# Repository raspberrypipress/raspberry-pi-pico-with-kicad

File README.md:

# Design an RP2040 board with KiCad

Example code and assets for Design an RP2040 board with KiCad from Raspberry Pi Press

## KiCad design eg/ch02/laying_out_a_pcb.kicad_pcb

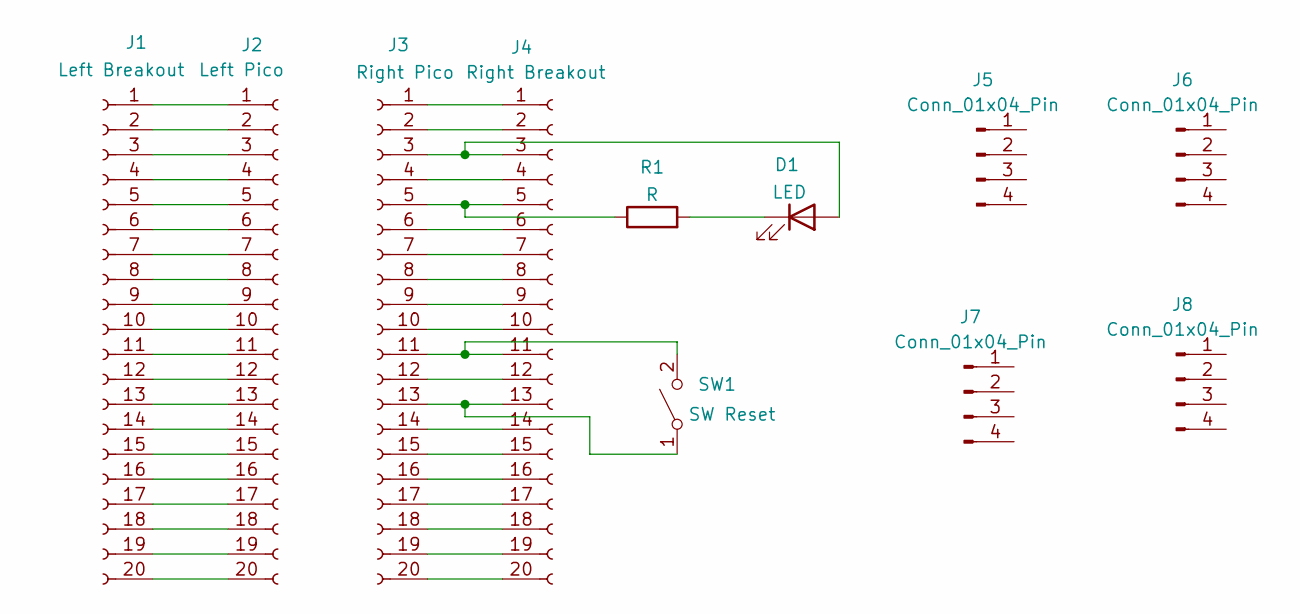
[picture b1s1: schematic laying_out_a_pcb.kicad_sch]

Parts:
D1: LED; LED_0805_2012Metric
J1: Left Breakout; PinSocket_1x20_P2.54mm_Vertical
J2: Left Pico; PinSocket_1x20_P2.54mm_Vertical
J3: Right Pico; PinSocket_1x20_P2.54mm_Vertical
J4: Right Breakout; PinSocket_1x20_P2.54mm_Vertical
J5, J6, J7, J8: Conn_01x04_Pin; PinSocket_1x04_P2.54mm_Vertical
R1: R; R_0805_2012Metric
SW1: SW Reset; SW_SPST_B3SL-1002P

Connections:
unnamed 0: D1.2 (A), J3.3, J4.3; also elsewhere on the board
unnamed 1: D1.1 (K), R1.2; also elsewhere on the board
unnamed: J1.1, J2.1
unnamed: J1.2, J2.2
unnamed: J1.3, J2.3
unnamed: J1.4, J2.4
unnamed: J1.5, J2.5
unnamed: J1.6, J2.6
unnamed: J1.7, J2.7
unnamed: J1.8, J2.8
unnamed: J1.9, J2.9
unnamed: J1.10, J2.10
unnamed: J1.11, J2.11
unnamed: J1.12, J2.12
unnamed: J1.13, J2.13
unnamed: J1.14, J2.14
unnamed: J1.15, J2.15
unnamed: J1.16, J2.16
unnamed: J1.17, J2.17
unnamed: J1.18, J2.18
unnamed: J1.19, J2.19
unnamed: J1.20, J2.20
unnamed: J3.1, J4.1
unnamed: J3.2, J4.2
unnamed: J3.4, J4.4
unnamed: J3.5, J4.5, R1.1
unnamed: J3.6, J4.6
unnamed: J3.7, J4.7
unnamed: J3.8, J4.8
unnamed: J3.9, J4.9
unnamed: J3.10, J4.10
unnamed: J3.11, J4.11, SW1.2 (B)
unnamed: J3.12, J4.12
unnamed: J3.13, J4.13, SW1.1 (A)
unnamed: J3.14, J4.14
unnamed: J3.15, J4.15
unnamed: J3.16, J4.16
unnamed: J3.17, J4.17
unnamed: J3.18, J4.18
unnamed: J3.19, J4.19
unnamed: J3.20, J4.20

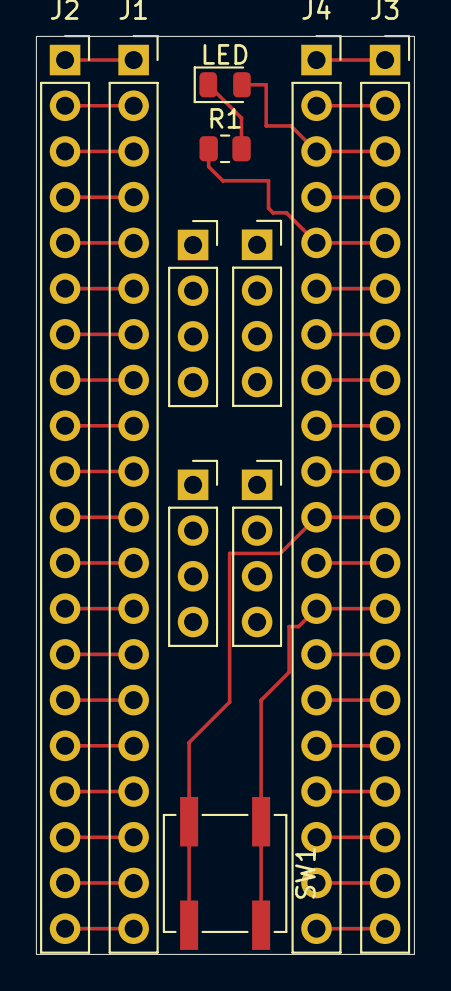
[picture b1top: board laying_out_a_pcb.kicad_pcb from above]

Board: 2 copper layers, 21.0 x 51.0 mm, 11 parts (0 on the bottom side), 41 nets.

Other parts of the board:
LED: LED; LED_0805_2012Metric

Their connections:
unnamed 0: LED.2 (A); also elsewhere on the board
unnamed 1: LED.1 (K); also elsewhere on the board

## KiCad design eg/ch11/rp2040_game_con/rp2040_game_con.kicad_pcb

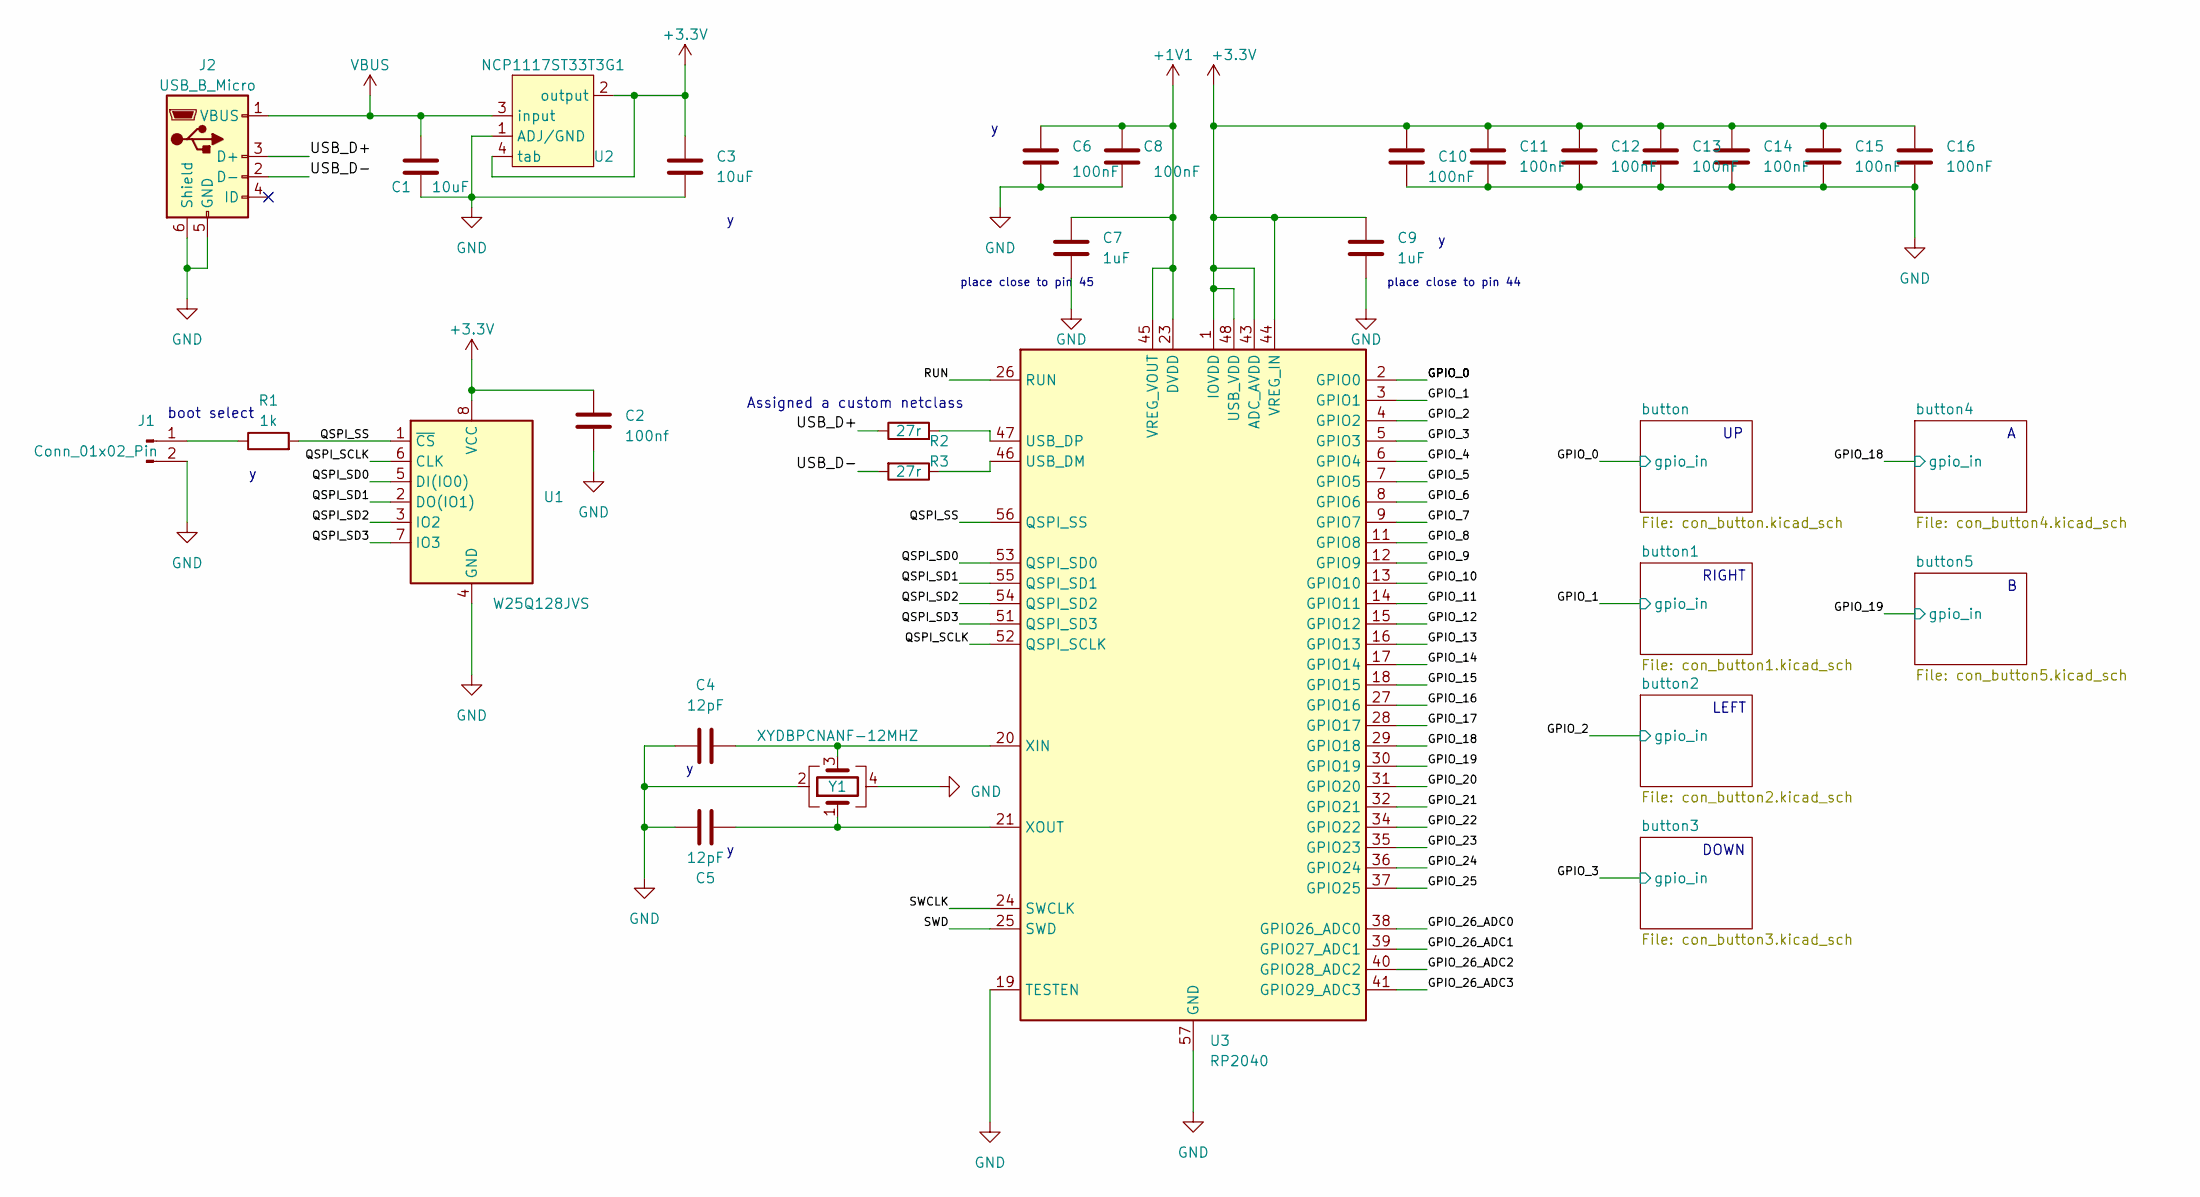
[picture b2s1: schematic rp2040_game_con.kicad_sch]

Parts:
C1, C3: 10uF; C_1206_3216Metric; LCSC C13585
C2: 100nf; C_0402_1005Metric; LCSC C1525
C4, C5: 12pF; C_0402_1005Metric; LCSC C1547
C6, C8, C10, C11, C12, C13, C15, C16: 100nF; C_0402_1005Metric; LCSC C1525
C7, C9: 1uF; C_0402_1005Metric; LCSC C52923
C14: 100nF; C_0402_1005Metric; JLCPCBA Part # C1525
J1: Conn_01x02_Pin; PinHeader_1x02_P2.54mm_Vertical
J2: USB_B_Micro; MICRO-USB-SMD_C393940; LCSC C393940
R1: 1k; R_0402_1005Metric; LCSC C279981
R2, R3: 27r; R_0402_1005Metric; LCSC C2909343
U1: W25Q128JVS; SOIC-8_5.23x5.23mm_P1.27mm; LCSC C97521
U2: NCP1117ST33T3G1; SOT-223; LCSC C6186
U3: RP2040; QFN-56-1EP_7x7mm_P0.4mm_EP3.2x3.2mm; LCSC C2040
Y1: XYDBPCNANF-12MHZ; Xstal_2520_4P_XYDBPCNANF-12MHZ; LCSC C521567

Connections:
+1V1: C6.1, C7.1, C8.1, U3.23 (DVDD), U3.45 (VREG_VOUT), U3.50 (DVDD)
+3.3V: C2.1, C3.1, C9.1, C10.1, C11.1, C12.1, C13.1, C14.1, C15.1, C16.1, U1.8 (VCC), U2.2 (output), U2.4 (tab), U3.1 (IOVDD), U3.10 (IOVDD), U3.22 (IOVDD), U3.33 (IOVDD), U3.42 (IOVDD), U3.43 (ADC_AVDD), U3.44 (VREG_IN), U3.48 (USB_VDD), U3.49 (IOVDD)
/GPIO_0: U3.2 (GPIO0); also elsewhere on the board
/GPIO_1: U3.3 (GPIO1); also elsewhere on the board
/GPIO_2: U3.4 (GPIO2); also elsewhere on the board
/GPIO_3: U3.5 (GPIO3); also elsewhere on the board
/GPIO_4: U3.6 (GPIO4)
/GPIO_5: U3.7 (GPIO5)
/GPIO_6: U3.8 (GPIO6)
/GPIO_7: U3.9 (GPIO7)
/GPIO_8: U3.11 (GPIO8)
/GPIO_9: U3.12 (GPIO9)
/GPIO_10: U3.13 (GPIO10)
/GPIO_11: U3.14 (GPIO11)
/GPIO_12: U3.15 (GPIO12)
/GPIO_13: U3.16 (GPIO13)
/GPIO_14: U3.17 (GPIO14)
/GPIO_15: U3.18 (GPIO15)
/GPIO_16: U3.27 (GPIO16)
/GPIO_17: U3.28 (GPIO17)
/GPIO_18: U3.29 (GPIO18); also elsewhere on the board
/GPIO_19: U3.30 (GPIO19); also elsewhere on the board
/GPIO_20: U3.31 (GPIO20)
/GPIO_21: U3.32 (GPIO21)
/GPIO_22: U3.34 (GPIO22)
/GPIO_23: U3.35 (GPIO23)
/GPIO_24: U3.36 (GPIO24)
/GPIO_25: U3.37 (GPIO25)
/GPIO_26_ADC0: U3.38 (GPIO26_ADC0)
/GPIO_26_ADC1: U3.39 (GPIO27_ADC1)
/GPIO_26_ADC2: U3.40 (GPIO28_ADC2)
/GPIO_26_ADC3: U3.41 (GPIO29_ADC3)
/QSPI_SCLK: U1.6 (CLK), U3.52 (QSPI_SCLK)
/QSPI_SD0: U1.5 (DI(IO0)), U3.53 (QSPI_SD0)
/QSPI_SD1: U1.2 (DO(IO1)), U3.55 (QSPI_SD1)
/QSPI_SD2: U1.3 (IO2), U3.54 (QSPI_SD2)
/QSPI_SD3: U1.7 (IO3), U3.51 (QSPI_SD3)
/QSPI_SS: R1.2, U1.1 (~CS), U3.56 (QSPI_SS)
/RUN: U3.26 (RUN)
/SWCLK: U3.24 (SWCLK)
/SWD: U3.25 (SWD)
/USB_D+: J2.3 (D+), R2.1
/USB_D-: J2.2 (D-), R3.2
GND: C1.2, C2.2, C3.2, C4.1, C5.1, C6.2, C7.2, C8.2, C9.2, C10.2, C11.2, C12.2, C13.2, C14.2, C15.2, C16.2, J1.2, J2.5 (GND), J2.6 (Shield), U1.4 (GND), U2.1 (ADJ/GND), U3.19 (TESTEN), U3.57 (GND), Y1.2, Y1.4; also elsewhere on the board
unnamed: J1.1, R1.1
unnamed: R3.1, U3.46 (USB_DM)
unnamed: R2.2, U3.47 (USB_DP)
unnamed: C4.2, U3.20 (XIN), Y1.3
unnamed: C5.2, U3.21 (XOUT), Y1.1
VBUS: C1.1, J2.1 (VBUS), U2.3 (input)

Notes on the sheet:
DOWN
place close to pin 45
LEFT
boot select
RIGHT
place close to pin 44
Assigned a custom netclass

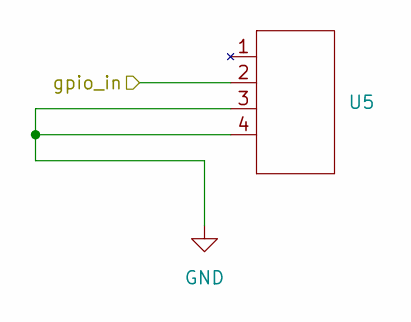
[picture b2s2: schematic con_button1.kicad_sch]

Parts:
U5: Game_Conn_Button_C221902; LCSC C221902

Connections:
/GPIO_1: U5.2; also elsewhere on the board
GND: U5.3, U5.4; also elsewhere on the board

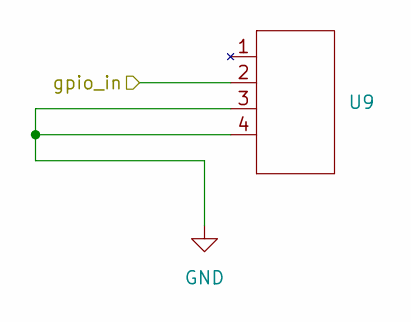
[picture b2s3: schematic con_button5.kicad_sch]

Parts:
U9: Game_Conn_Button_C221902; LCSC C221902

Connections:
/GPIO_19: U9.2; also elsewhere on the board
GND: U9.3, U9.4; also elsewhere on the board

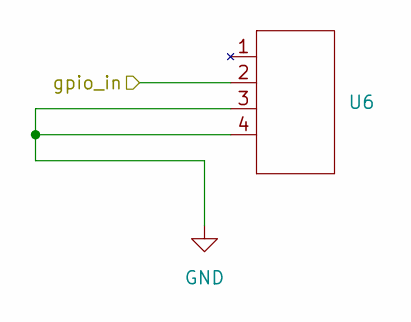
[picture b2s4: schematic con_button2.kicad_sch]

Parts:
U6: Game_Conn_Button_C221902; LCSC C221902

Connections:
/GPIO_2: U6.2; also elsewhere on the board
GND: U6.3, U6.4; also elsewhere on the board

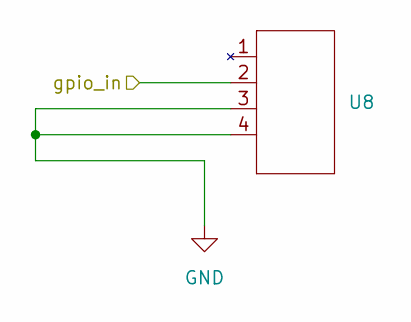
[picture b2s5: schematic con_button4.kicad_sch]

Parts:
U8: Game_Conn_Button_C221902; LCSC C221902

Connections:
/GPIO_18: U8.2; also elsewhere on the board
GND: U8.3, U8.4; also elsewhere on the board

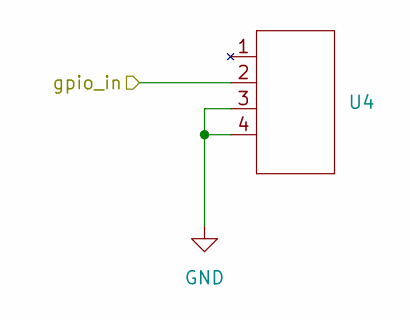
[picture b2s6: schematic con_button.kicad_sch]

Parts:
U4: Game_Conn_Button_C221902; LCSC C221902

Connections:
/GPIO_0: U4.2; also elsewhere on the board
GND: U4.3, U4.4; also elsewhere on the board

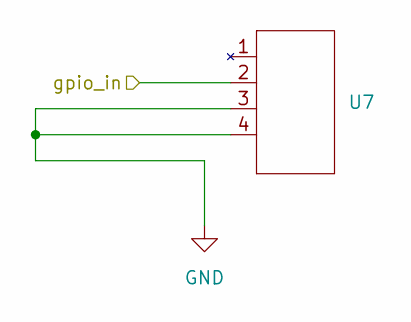
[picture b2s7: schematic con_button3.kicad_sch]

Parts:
U7: Game_Conn_Button_C221902; LCSC C221902

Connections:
/GPIO_3: U7.2; also elsewhere on the board
GND: U7.3, U7.4; also elsewhere on the board

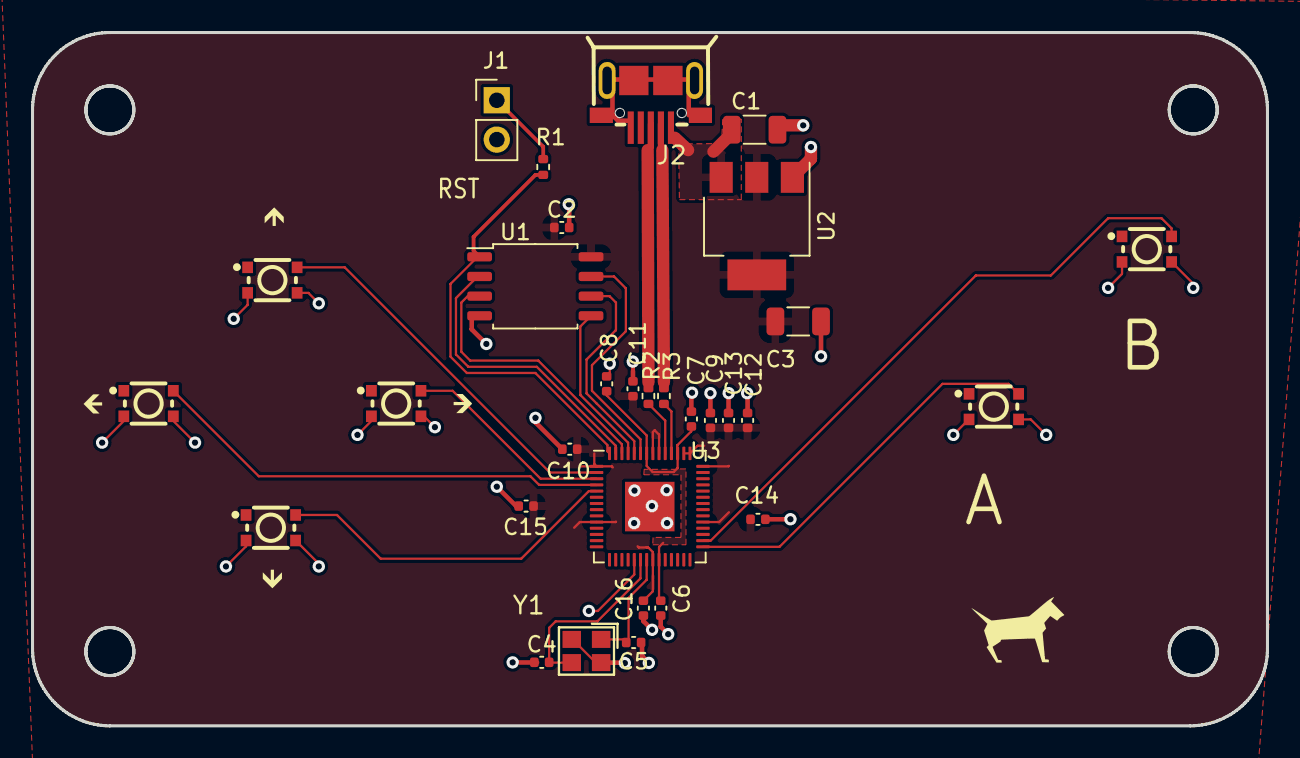
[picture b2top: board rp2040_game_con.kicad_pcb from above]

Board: 2 copper layers, 79.8 x 44.8 mm, 31 parts (0 on the bottom side), 23 nets.

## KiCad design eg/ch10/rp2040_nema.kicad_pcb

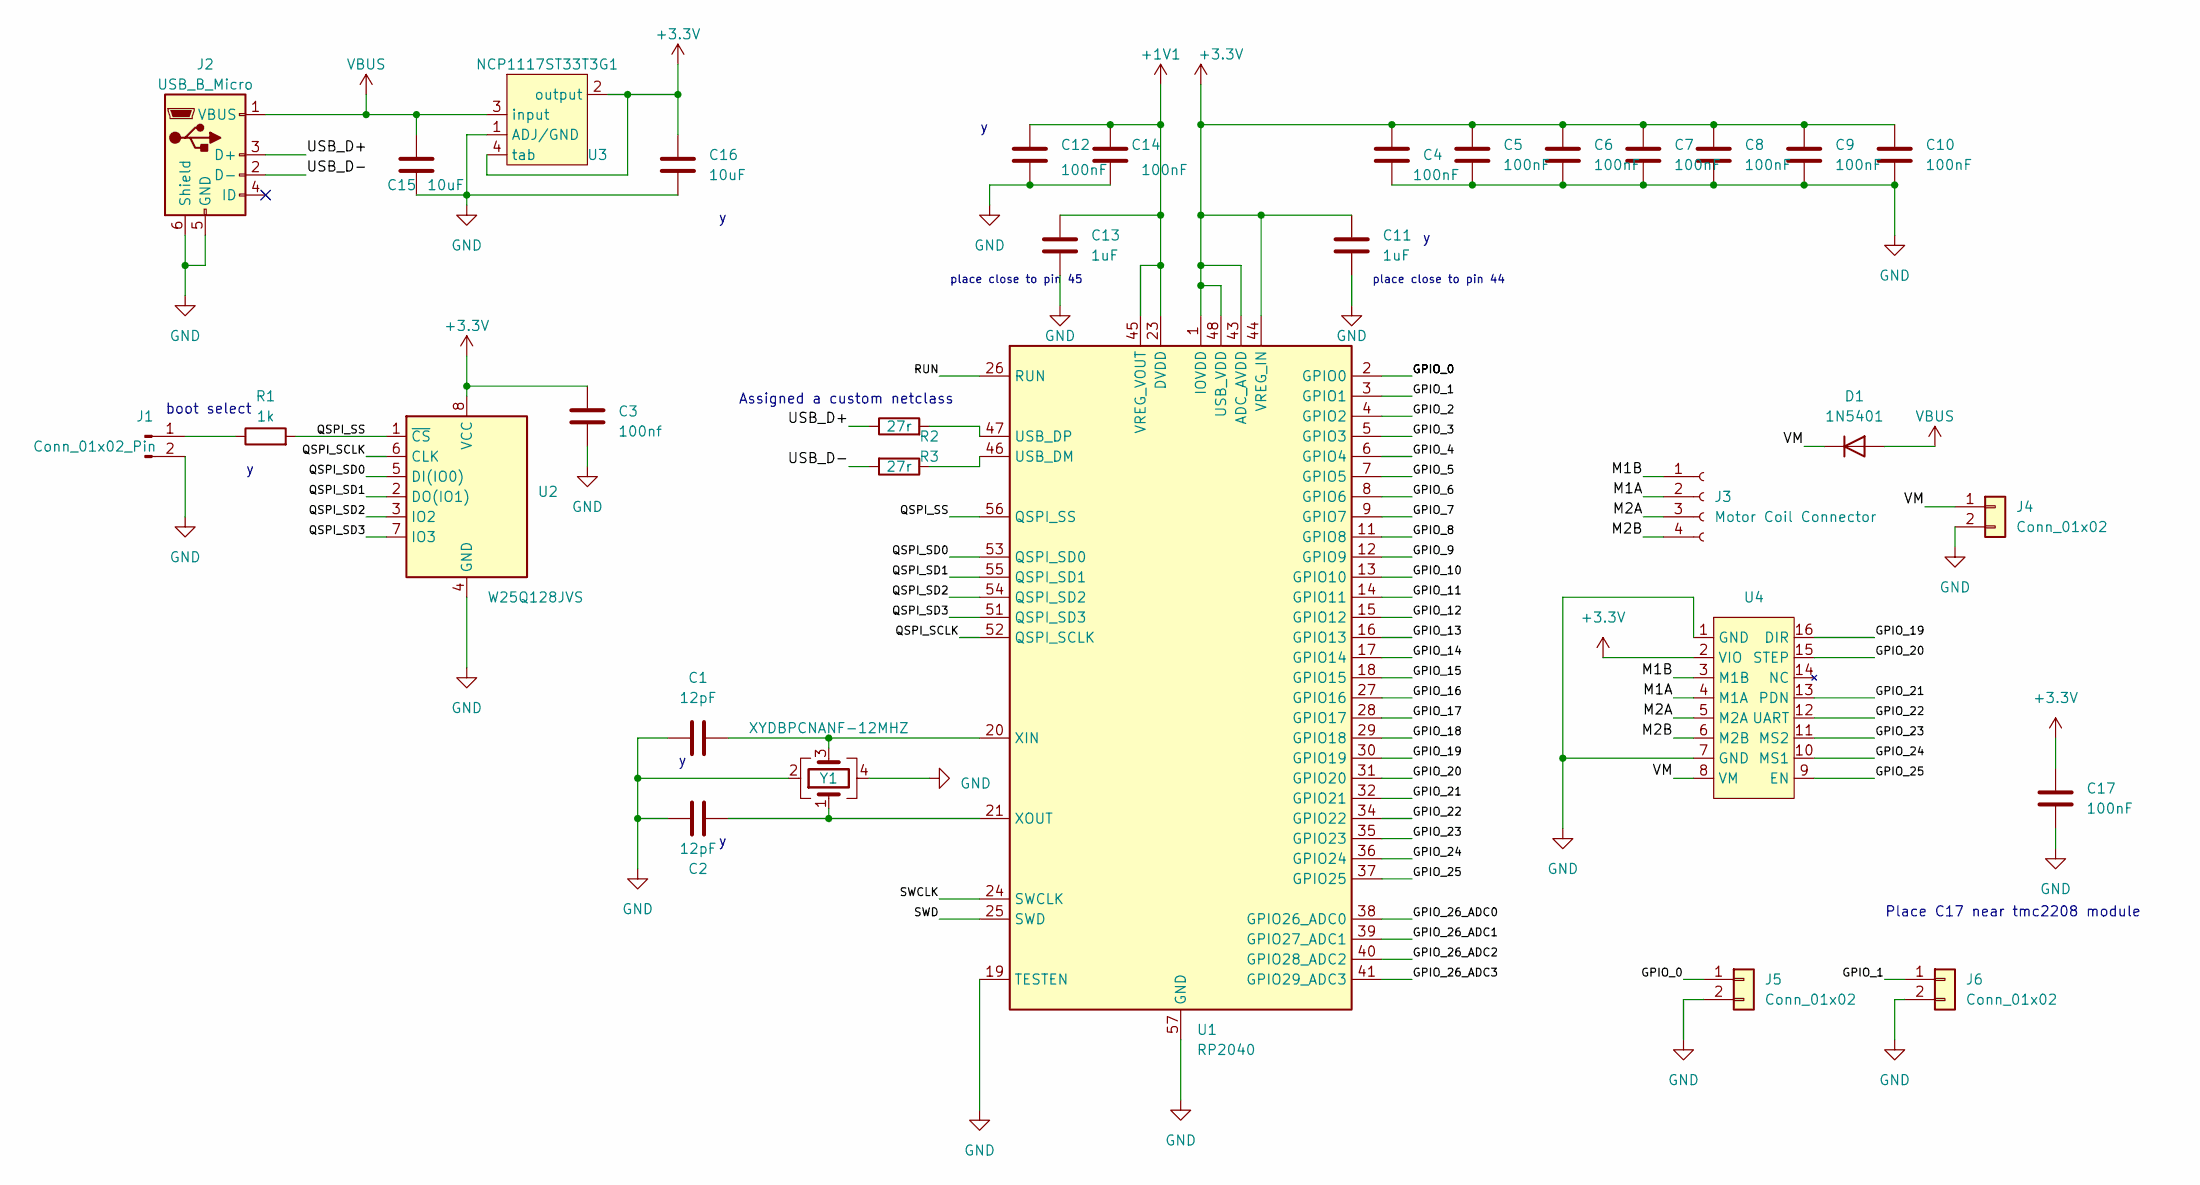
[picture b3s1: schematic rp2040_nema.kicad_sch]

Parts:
C1, C2: 12pF; C_0402_1005Metric; LCSC C1547
C3: 100nf; C_0402_1005Metric; LCSC C1525
C4, C5, C6, C7, C9, C10, C12, C14, C17: 100nF; C_0402_1005Metric; LCSC C1525
C8: 100nF; C_0402_1005Metric; JLCPCBA Part # C1525
C11, C13: 1uF; C_0402_1005Metric; LCSC C52923
C15, C16: 10uF; C_1206_3216Metric; LCSC C13585
D1: 1N5401; Diode_Schottky_SMB(DO-214AA); LCSC C908684
J1: Conn_01x02_Pin; PinHeader_1x02_P2.54mm_Vertical
J2: USB_B_Micro; MICRO-USB-SMD_C393940; LCSC C393940
J3: Motor Coil Connector; PinHeader_1x04_P2.54mm_Vertical
J4, J5, J6: Conn_01x02; PinHeader_1x02_P2.54mm_Vertical
R1: 1k; R_0402_1005Metric; LCSC C279981
R2, R3: 27r; R_0402_1005Metric; LCSC C2909343
U1: RP2040; QFN-56-1EP_7x7mm_P0.4mm_EP3.2x3.2mm; LCSC C2040
U2: W25Q128JVS; SOIC-8_5.23x5.23mm_P1.27mm; LCSC C97521
U3: NCP1117ST33T3G1; SOT-223; LCSC C6186
U4: TMC2208_Module
Y1: XYDBPCNANF-12MHZ; Xstal_2520_4P_XYDBPCNANF-12MHZ; LCSC C521567

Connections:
+1V1: C12.1, C13.1, C14.1, U1.23 (DVDD), U1.45 (VREG_VOUT), U1.50 (DVDD)
+3.3V: C3.1, C4.1, C5.1, C6.1, C7.1, C8.1, C9.1, C10.1, C11.1, C16.1, C17.1, U1.1 (IOVDD), U1.10 (IOVDD), U1.22 (IOVDD), U1.33 (IOVDD), U1.42 (IOVDD), U1.43 (ADC_AVDD), U1.44 (VREG_IN), U1.48 (USB_VDD), U1.49 (IOVDD), U2.8 (VCC), U3.2 (output), U3.4 (tab), U4.2 (VIO)
/GPIO_0: J5.1, U1.2 (GPIO0)
/GPIO_1: J6.1, U1.3 (GPIO1)
/GPIO_2: U1.4 (GPIO2)
/GPIO_3: U1.5 (GPIO3)
/GPIO_4: U1.6 (GPIO4)
/GPIO_5: U1.7 (GPIO5)
/GPIO_6: U1.8 (GPIO6)
/GPIO_7: U1.9 (GPIO7)
/GPIO_8: U1.11 (GPIO8)
/GPIO_9: U1.12 (GPIO9)
/GPIO_10: U1.13 (GPIO10)
/GPIO_11: U1.14 (GPIO11)
/GPIO_12: U1.15 (GPIO12)
/GPIO_13: U1.16 (GPIO13)
/GPIO_14: U1.17 (GPIO14)
/GPIO_15: U1.18 (GPIO15)
/GPIO_16: U1.27 (GPIO16)
/GPIO_17: U1.28 (GPIO17)
/GPIO_18: U1.29 (GPIO18)
/GPIO_19: U1.30 (GPIO19), U4.16 (DIR)
/GPIO_20: U1.31 (GPIO20), U4.15 (STEP)
/GPIO_21: U1.32 (GPIO21), U4.13 (PDN)
/GPIO_22: U1.34 (GPIO22), U4.12 (UART)
/GPIO_23: U1.35 (GPIO23), U4.11 (MS2)
/GPIO_24: U1.36 (GPIO24), U4.10 (MS1)
/GPIO_25: U1.37 (GPIO25), U4.9 (EN)
/GPIO_26_ADC0: U1.38 (GPIO26_ADC0)
/GPIO_26_ADC1: U1.39 (GPIO27_ADC1)
/GPIO_26_ADC2: U1.40 (GPIO28_ADC2)
/GPIO_26_ADC3: U1.41 (GPIO29_ADC3)
/M1A: J3.2, U4.4 (M1A)
/M1B: J3.1, U4.3 (M1B)
/M2A: J3.3, U4.5 (M2A)
/M2B: J3.4, U4.6 (M2B)
/QSPI_SCLK: U1.52 (QSPI_SCLK), U2.6 (CLK)
/QSPI_SD0: U1.53 (QSPI_SD0), U2.5 (DI(IO0))
/QSPI_SD1: U1.55 (QSPI_SD1), U2.2 (DO(IO1))
/QSPI_SD2: U1.54 (QSPI_SD2), U2.3 (IO2)
/QSPI_SD3: U1.51 (QSPI_SD3), U2.7 (IO3)
/QSPI_SS: R1.2, U1.56 (QSPI_SS), U2.1 (~CS)
/RUN: U1.26 (RUN)
/SWCLK: U1.24 (SWCLK)
/SWD: U1.25 (SWD)
/USB_D+: J2.3 (D+), R2.1
/USB_D-: J2.2 (D-), R3.2
/VM: D1.1 (K), J4.1, U4.8 (VM)
GND: C1.1, C2.1, C3.2, C4.2, C5.2, C6.2, C7.2, C8.2, C9.2, C10.2, C11.2, C12.2, C13.2, C14.2, C15.2, C16.2, C17.2, J1.2, J2.5 (GND), J2.6 (Shield), J4.2, J5.2, J6.2, U1.19 (TESTEN), U1.57 (GND), U2.4 (GND), U3.1 (ADJ/GND), U4.1 (GND), U4.7 (GND), Y1.2, Y1.4
unnamed: J1.1, R1.1
unnamed: R3.1, U1.46 (USB_DM)
unnamed: R2.2, U1.47 (USB_DP)
unnamed: C1.2, U1.20 (XIN), Y1.3
unnamed: C2.2, U1.21 (XOUT), Y1.1
VBUS: C15.1, D1.2 (A), J2.1 (VBUS), U3.3 (input)

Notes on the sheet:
place close to pin 45
Place C17 near tmc2208 module
boot select
place close to pin 44
Assigned a custom netclass

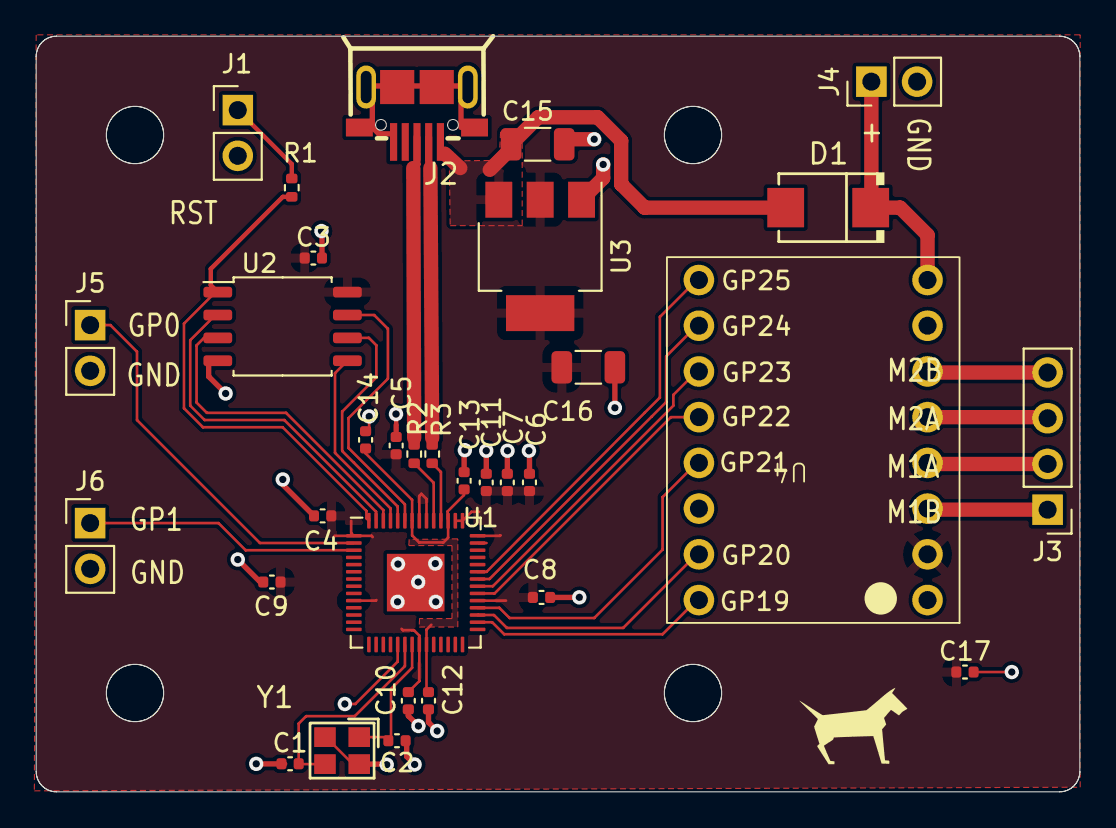
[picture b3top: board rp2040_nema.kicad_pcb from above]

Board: 2 copper layers, 58.0 x 42.0 mm, 32 parts (0 on the bottom side), 31 nets.

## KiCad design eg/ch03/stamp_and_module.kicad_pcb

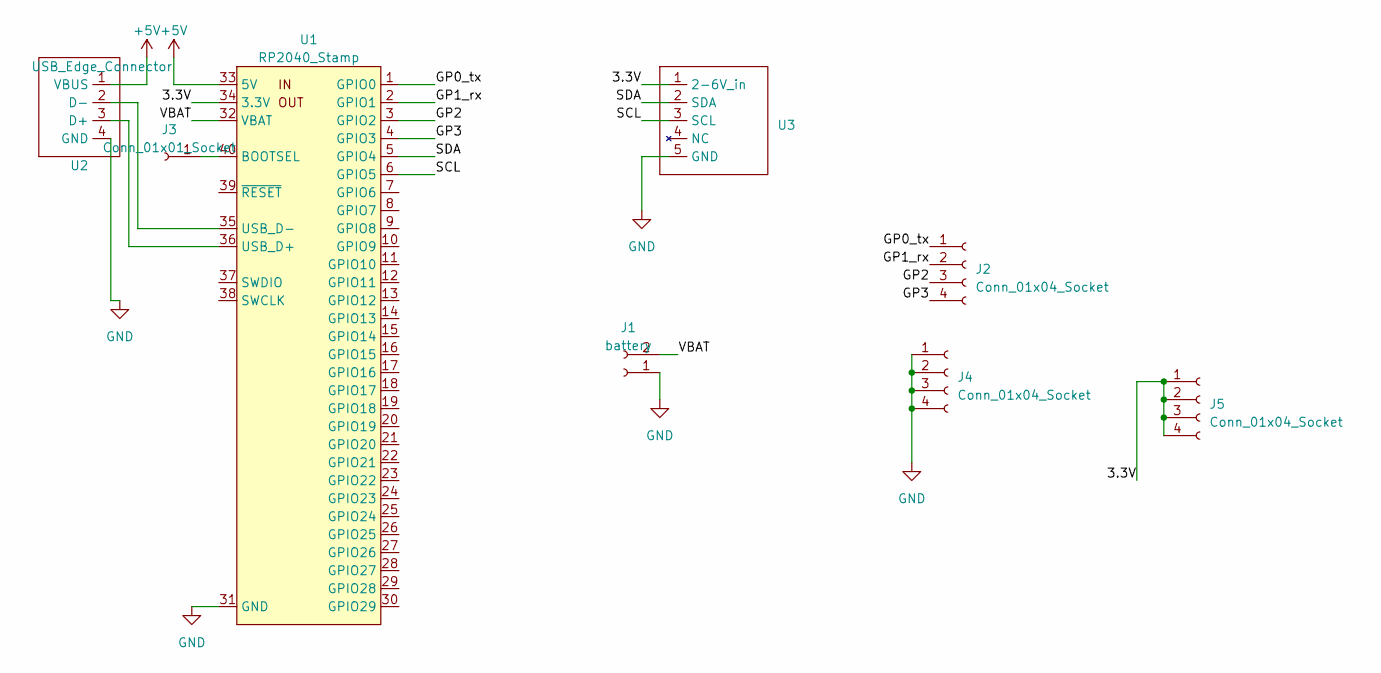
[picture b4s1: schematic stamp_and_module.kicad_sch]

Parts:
J1: battery; PinSocket_1x02_P2.54mm_Vertical
J2, J4, J5: Conn_01x04_Socket; PinSocket_1x04_P2.54mm_Vertical
J3: Conn_01x01_Socket; PinSocket_1x01_P2.54mm_Vertical
U1: RP2040_Stamp; RP2040_Stamp_THT
U2: USB_Edge_Connector; CD_usb_edge
U3: Pim_BMP280_Module

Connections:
+5V: U1.33 (5V), U2.1 (VBUS)
/3.3V: J5.1, J5.2, J5.3, J5.4, U1.34 (3.3V), U3.1 (2-6V_in)
/GP0_tx: J2.1, U1.1 (GPIO0)
/GP1_rx: J2.2, U1.2 (GPIO1)
/GP2: J2.3, U1.3 (GPIO2)
/GP3: J2.4, U1.4 (GPIO3)
/SCL: U1.6 (GPIO5), U3.3 (SCL)
/SDA: U1.5 (GPIO4), U3.2 (SDA)
/VBAT: J1.2, U1.32 (VBAT)
GND: J1.1, J4.1, J4.2, J4.3, J4.4, U1.31 (GND), U2.4 (GND), U3.5 (GND)
unnamed: J3.1, U1.40 (BOOTSEL)
unnamed: U1.36 (USB_D+), U2.3 (D+)
unnamed: U1.35 (USB_D-), U2.2 (D-)

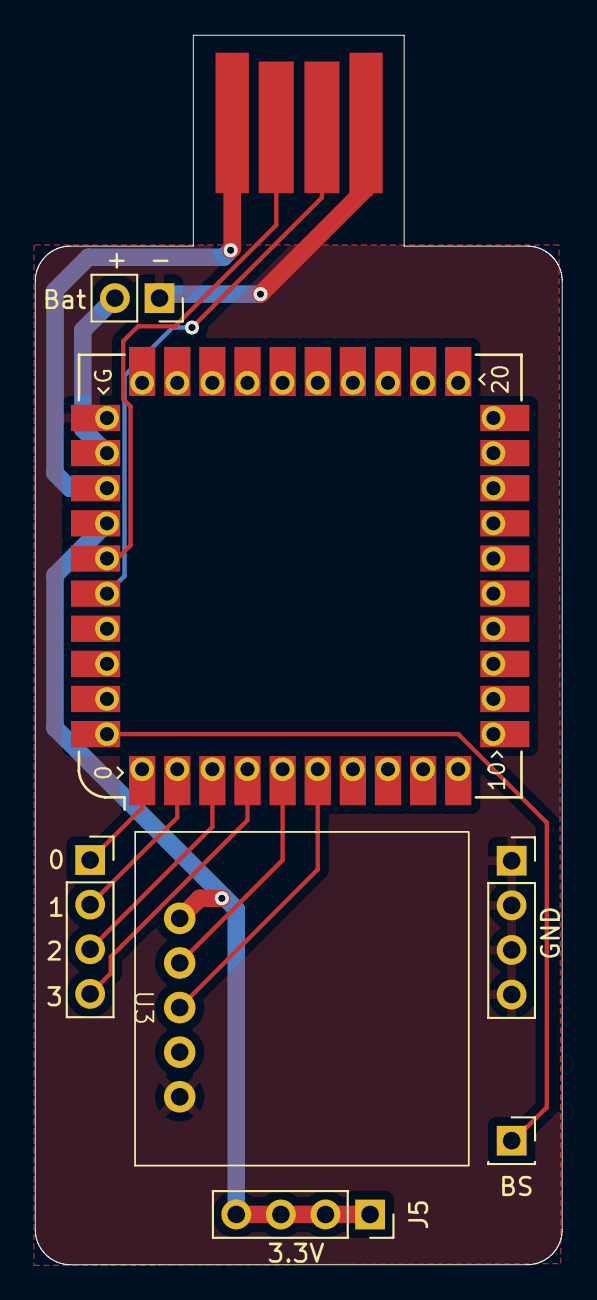
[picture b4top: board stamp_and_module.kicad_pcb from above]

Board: 2 copper layers, 30.0 x 70.0 mm, 8 parts (0 on the bottom side), 13 nets.

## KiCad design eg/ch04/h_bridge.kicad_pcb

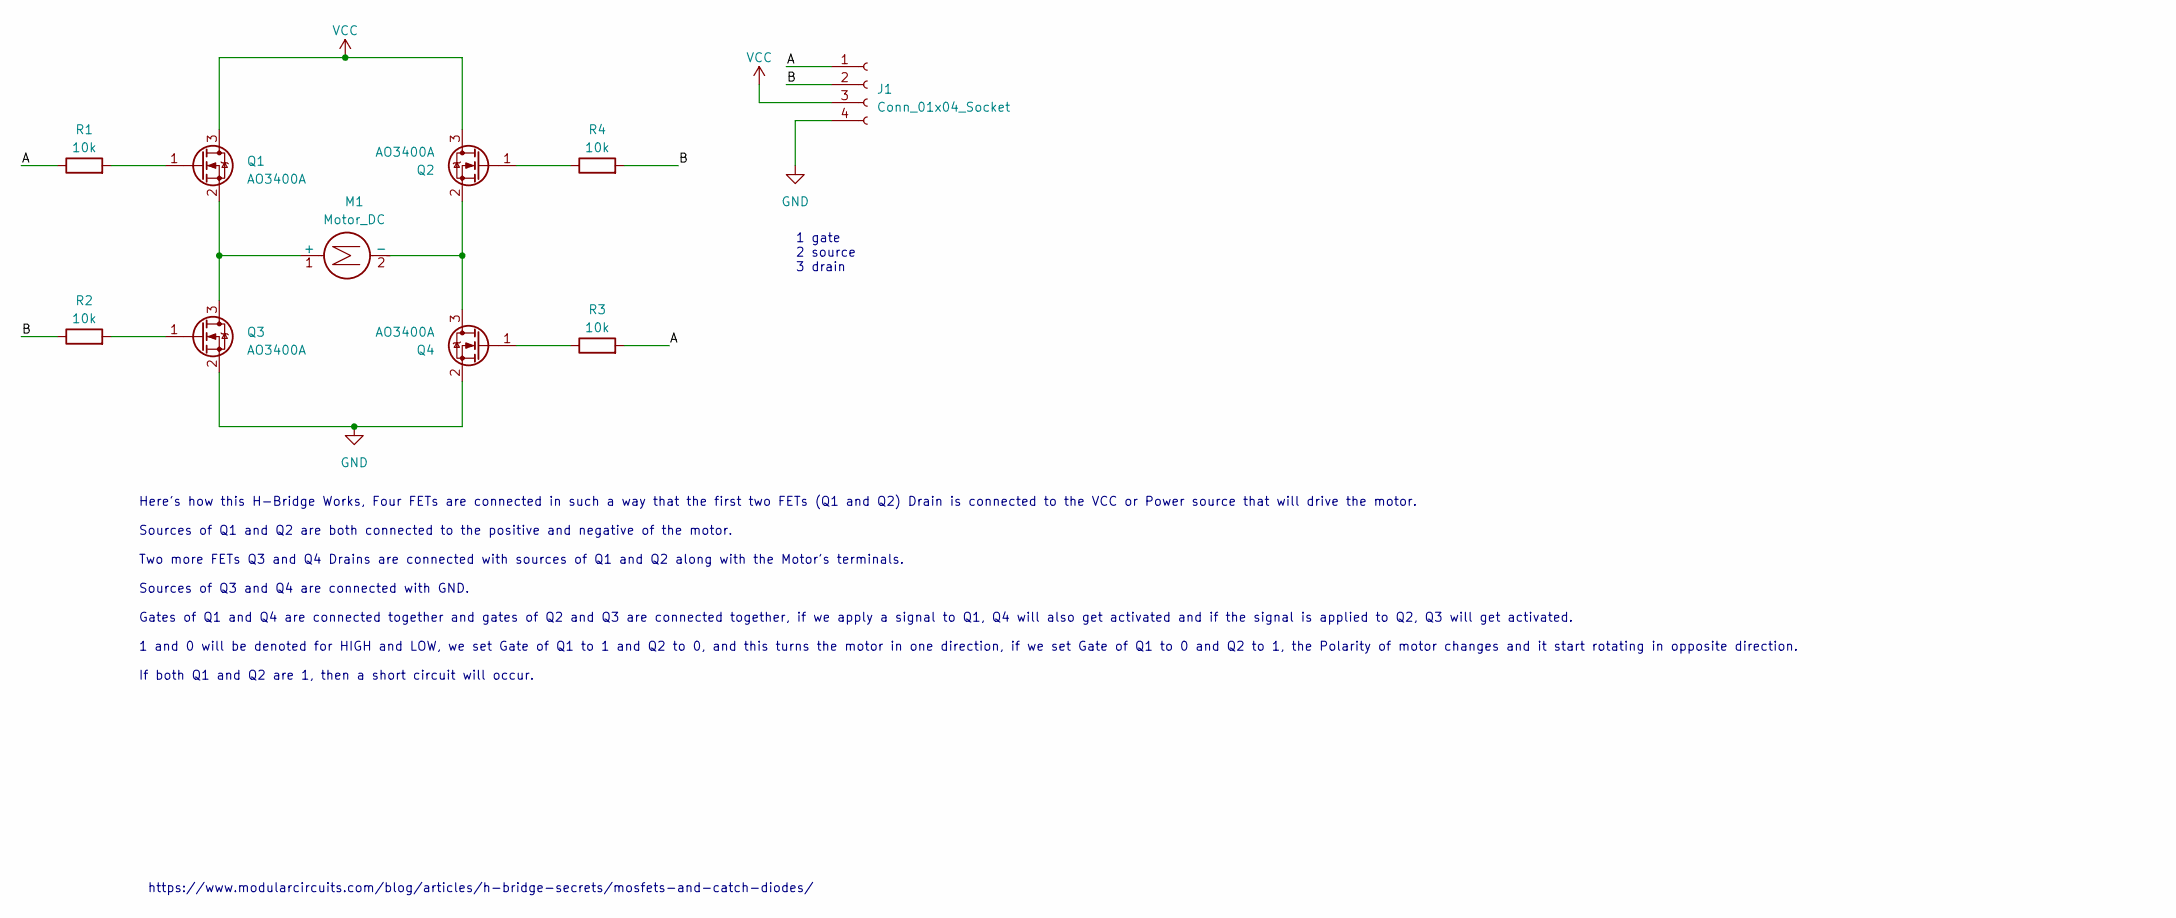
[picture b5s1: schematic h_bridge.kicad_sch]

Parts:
J1: Conn_01x04_Socket; PinHeader_1x04_P2.54mm_Vertical
M1: Motor_DC; PinHeader_1x02_P2.54mm_Vertical
Q1, Q2, Q3, Q4: AO3400A; SOT-23; LCSC C20917
R1, R2, R3, R4: 10k; R_0805_2012Metric; LCSC C491222

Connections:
/A: J1.1, R1.1, R3.2
/B: J1.2, R2.1, R4.2
GND: J1.4, Q3.2 (S), Q4.2 (S)
unnamed: M1.1 (+), Q1.2 (S), Q3.3 (D)
unnamed: M1.2 (-), Q2.2 (S), Q4.3 (D)
unnamed: Q1.1 (G), R1.2
unnamed: Q2.1 (G), R4.1
unnamed: Q3.1 (G), R2.2
unnamed: Q4.1 (G), R3.1
VCC: J1.3, Q1.3 (D), Q2.3 (D)

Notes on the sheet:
Here's how this H-Bridge Works, Four FETs are connected in such a way that the first two FETs (Q1 and Q2) Drain is connected to the VCC or Power source that will drive the motor. Sources of Q1 and Q2 are both connected to the positive and negative of the motor. Two more FETs Q3 and Q4 Drains are co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
https://www.modularcircuits.com/blog/articles/h-bridge-secrets/mosfets-and-catch-diodes/
1 gate 2 source 3 drain

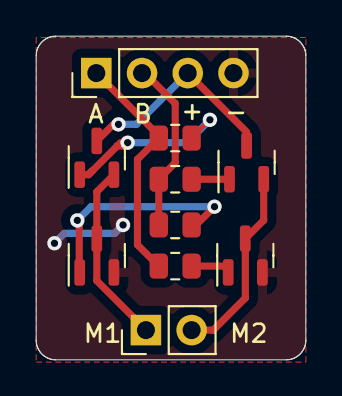
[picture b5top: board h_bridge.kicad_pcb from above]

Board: 2 copper layers, 15.0 x 18.0 mm, 10 parts (0 on the bottom side), 10 nets.

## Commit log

2024-08-05 added examples from ch03
2024-08-07 added chapter 4 files
2024-08-14 ch05 example
2024-08-17 moved to parent
2024-08-17 ch10 example
2024-08-17 added example code
2024-08-19 added license
2024-11-29 added issue template
2025-01-28 Added figures from the book
2025-04-11 adding ch01 example
2025-08-08 added Chapter 2 example
